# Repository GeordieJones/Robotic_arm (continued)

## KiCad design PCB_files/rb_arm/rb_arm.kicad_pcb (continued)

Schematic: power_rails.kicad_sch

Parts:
2.2uH1, 2.2uH2: L_Ferrite; L_0402_1005Metric; part number BLM15PX601SN1D
C88, C89, C96, C97: 22u; C_0402_1005Metric; part Murata Electronics GRM158R61A226ME15D
C90, C92, C93, C95: 4.7u; C_0402_1005Metric; part Samsung Electro-Mechanics CL05A475MP5NR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
C91, C94: 100n; C_0402_1005Metric; part samsung CL05B104KP5NNNC
L4: 2.2u; L_Wuerth_MAPI-4020
R30: 100; R_0402_1005Metric; part YAGEO RC0402FR-07100RL
R31, R32: 10k; R_0402_1005Metric; part number Samsung Electro-Mechanics RC1005F103CS
R33: 2.2k; R_0402_1005Metric; part number YAGEO RC0402FR-072K2L
TP7: 3V3A_TP; Pin_D1.0mm_L10.0mm
TP8: 1V8A_TP; Pin_D1.0mm_L10.0mm
TP9: 1V8_TP; Pin_D1.0mm_L10.0mm
TP10: 3V3_TP; Pin_D1.0mm_L10.0mm
U8: AP62150Z6; SOT-563
U9: LP5907MFX-3.3; SOT-23-5
U10: MCP1700T-1802E/MB; SOT-89-3
U11: TPS63001; Texas_DRC0010J_ThermalVias

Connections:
1V8: C96.2, L4.2, R33.2, TP9.1 (1_1); also elsewhere on the board
1V8A: C95.1, TP8.1 (1_1), U10.3 (VO); also elsewhere on the board
3V3: 2.2uH2.1, C97.1, TP10.1 (1_1), U11.1 (VOUT), U11.10 (FB); also elsewhere on the board
3V3A: C93.1, TP7.1 (1_1), U9.5 (OUT); also elsewhere on the board
+5V: C88.1, C89.1, C90.1, R30.2, U8.1 (VIN), U8.5 (EN), U9.1 (IN), U9.3 (EN), U11.5 (VIN); also elsewhere on the board
/Power_rails/L1: 2.2uH1.2, U11.4 (L1)
/Power_rails/L2: 2.2uH1.1, U11.2 (L2)
/Power_rails/VINA: C91.2, R30.1, U11.6 (EN), U11.7 (PS/SYNC), U11.8 (VINA)
GND: C88.2, C89.2, C90.2, C91.1, C92.2, C93.2, C95.2, C96.1, C97.2, R31.2, U8.3 (GND), U9.2 (GND), U10.1 (GND), U11.3 (PGND), U11.9 (GND), U11.11 (PGND); also elsewhere on the board
unnamed: R32.1, R33.1
unnamed: C94.2, U8.4 (BST)
unnamed: R31.1, R32.2, U8.6 (FB)
unnamed: C94.1, L4.1, U8.2 (SW)
unnamed: 2.2uH2.2, C92.1, U10.2 (VI)

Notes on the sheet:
fully checked
5V to 3.3V analog
5V to 1.8V
5V to 3.3V
3v3 to 1.8 analog

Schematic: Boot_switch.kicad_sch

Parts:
R21: 10k; R_0402_1005Metric; part number Samsung Electro-Mechanics RC1005F103CS
SW2: SW_SPDT_321; SW_SPDT_PCM12; part number c&K JS102011SAQN
TP6: boot; Pin_D1.0mm_L10.0mm

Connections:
3V3: SW2.1 (C), TP6.1 (1_1); also elsewhere on the board
/BOOT0_stm: R21.2; also elsewhere on the board
GND: SW2.3 (A); also elsewhere on the board
unnamed: R21.1, SW2.2 (B)

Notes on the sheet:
BOOT Switch
SW_BOOT0

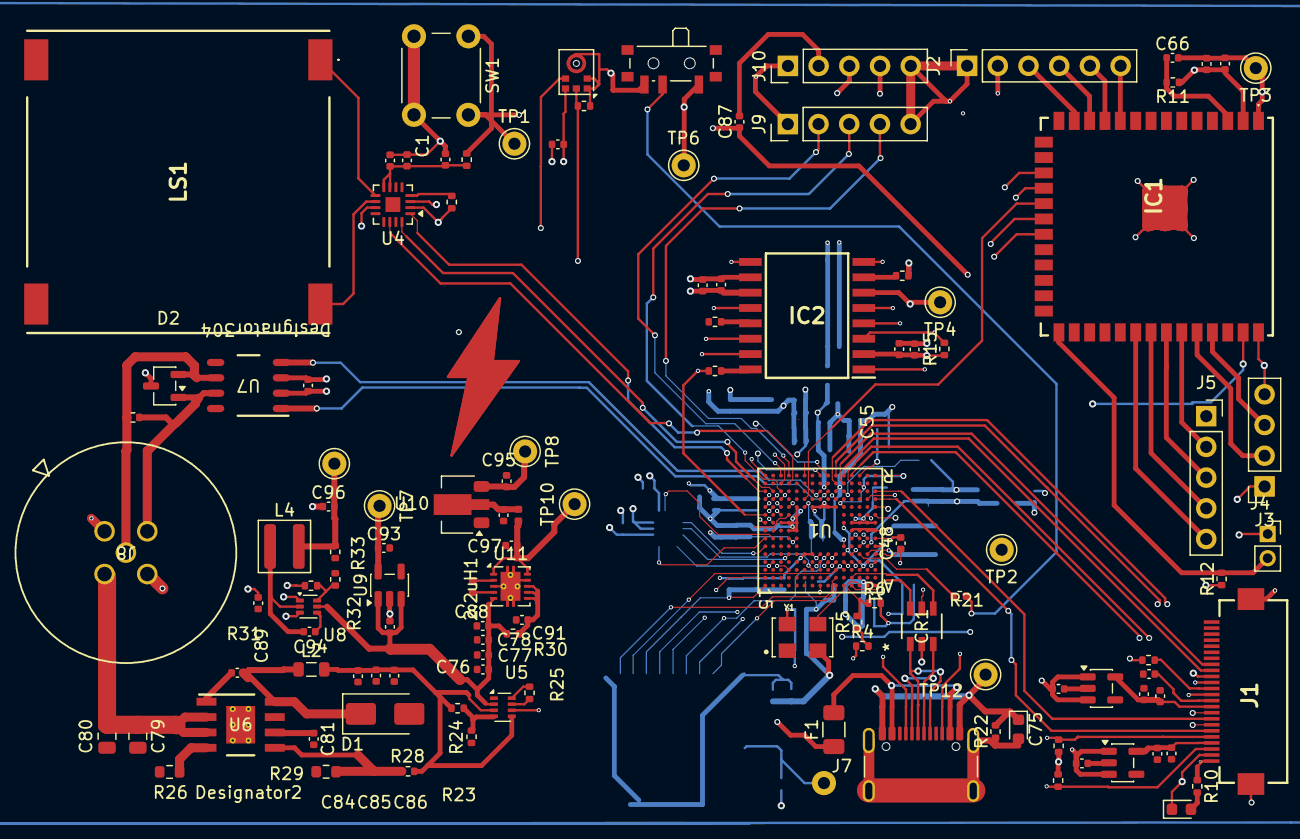
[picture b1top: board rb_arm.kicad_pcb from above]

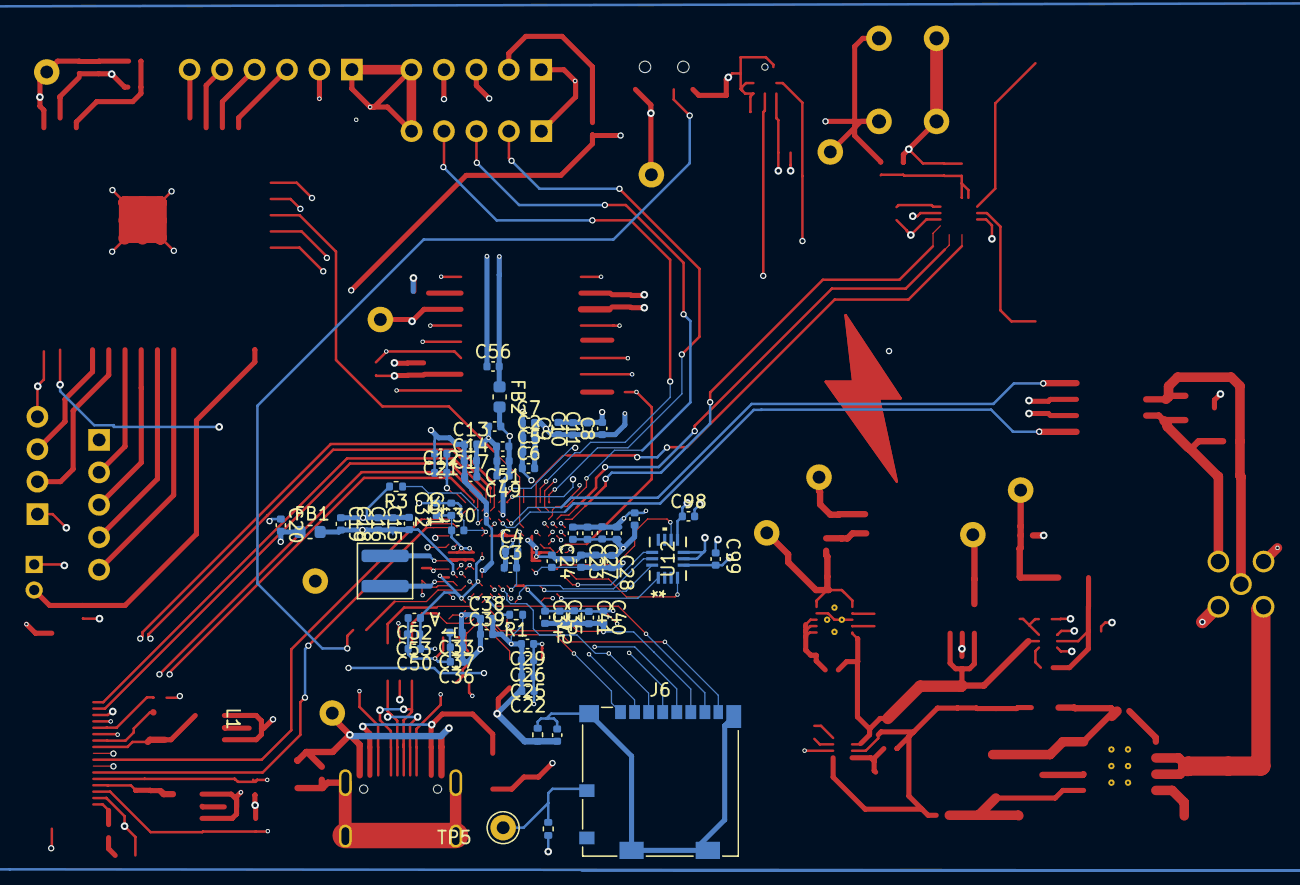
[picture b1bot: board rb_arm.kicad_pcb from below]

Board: 6 copper layers, 184 parts (67 on the bottom side), 127 nets.

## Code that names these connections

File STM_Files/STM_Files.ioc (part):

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Mcu.Name=STM32N647B0HxQ
Mcu.Package=VFBGA198
Mcu.UserName=STM32N647B0HxQ
PA11.Signal=FDCAN1_RX
PA12.Signal=FDCAN1_TX
PA13(JTMS/SWDIO).Signal=DEBUG_JTMS-SWDIO
PA14(JTCK/SWCLK).Signal=DEBUG_JTCK-SWCLK
PA15(JTDI).Signal=DEBUG_JTDI
PA3.Signal=SAI1_SD_B
PA6.Signal=SPI1_MISO
PA7.Signal=SPI1_MOSI
PB5(JTDO/TRACESWO).Signal=DEBUG_JTDO-SWO
PB6.Signal=SPI4_MISO
PB7.Signal=SPI4_MOSI
PC10.Signal=SDMMC1_D2
PC11.Signal=SDMMC1_D3
PC12.Signal=SDMMC1_CK
PC8.Signal=SDMMC1_D0
PC9.Signal=SDMMC1_D1
PE11.Signal=S_TIM1_CH2
PE12.Signal=SPI4_SCK
PE2.Signal=MDF1_CCK0
PE6.Signal=I2C1_SDA
PE8.Signal=MDF1_SDI0
PF11.GPIOParameters=PinAttribute
PF11.PinAttribute=Free
PF11.Signal=GPIO_Output
PF15.Signal=GPIO_Output
PF4.Signal=SPI1_NSS
PF5.GPIOParameters=PinAttribute
PF5.PinAttribute=Free
PF5.Signal=GPIO_Output
PF6.GPIOParameters=PinAttribute
PF6.PinAttribute=Free
PF6.Signal=GPIO_Output
PF7.Signal=SPI1_SCK
PG2.Signal=SAI1_FS_B
PG8.Signal=SAI1_SCK_B
PH0-OSC_IN(PH0).GPIOParameters=PinAttribute
PH0-OSC_IN(PH0).PinAttribute=Free
PH0-OSC_IN(PH0).Signal=RCC_OSC_IN
PH2.Signal=SDMMC1_CMD
PH9.Signal=I2C1_SCL
RCC.HSE_VALUE=48000000
board=custom
